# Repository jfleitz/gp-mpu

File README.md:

# GamePlan multi MPU board
This repository contains the KiCad files for designing and creating a GamePlan multi-mpu board for GamePlan pinball machines. The board will work in all upright as well as the cocktail pinball machines.

# Where to Order the board
PCBWay has the latest project files uploaded and verified. The link to order the boards can be found here:
https://www.pcbway.com/project/shareproject/GamePlan_Multi_MPU_Board_601e3e7b.html

# Assembly instructions
Robert Doerr of RobotWorkshop compiled a great assembly guide that can be found [here](docs/GP_Multi_Assembly_V1.3.pdf)

# Status
The board has been tested in several GamePlan machines, both upright and cocktail.

Checkout https://www.epinball.com for the background, current status and additional documentation.

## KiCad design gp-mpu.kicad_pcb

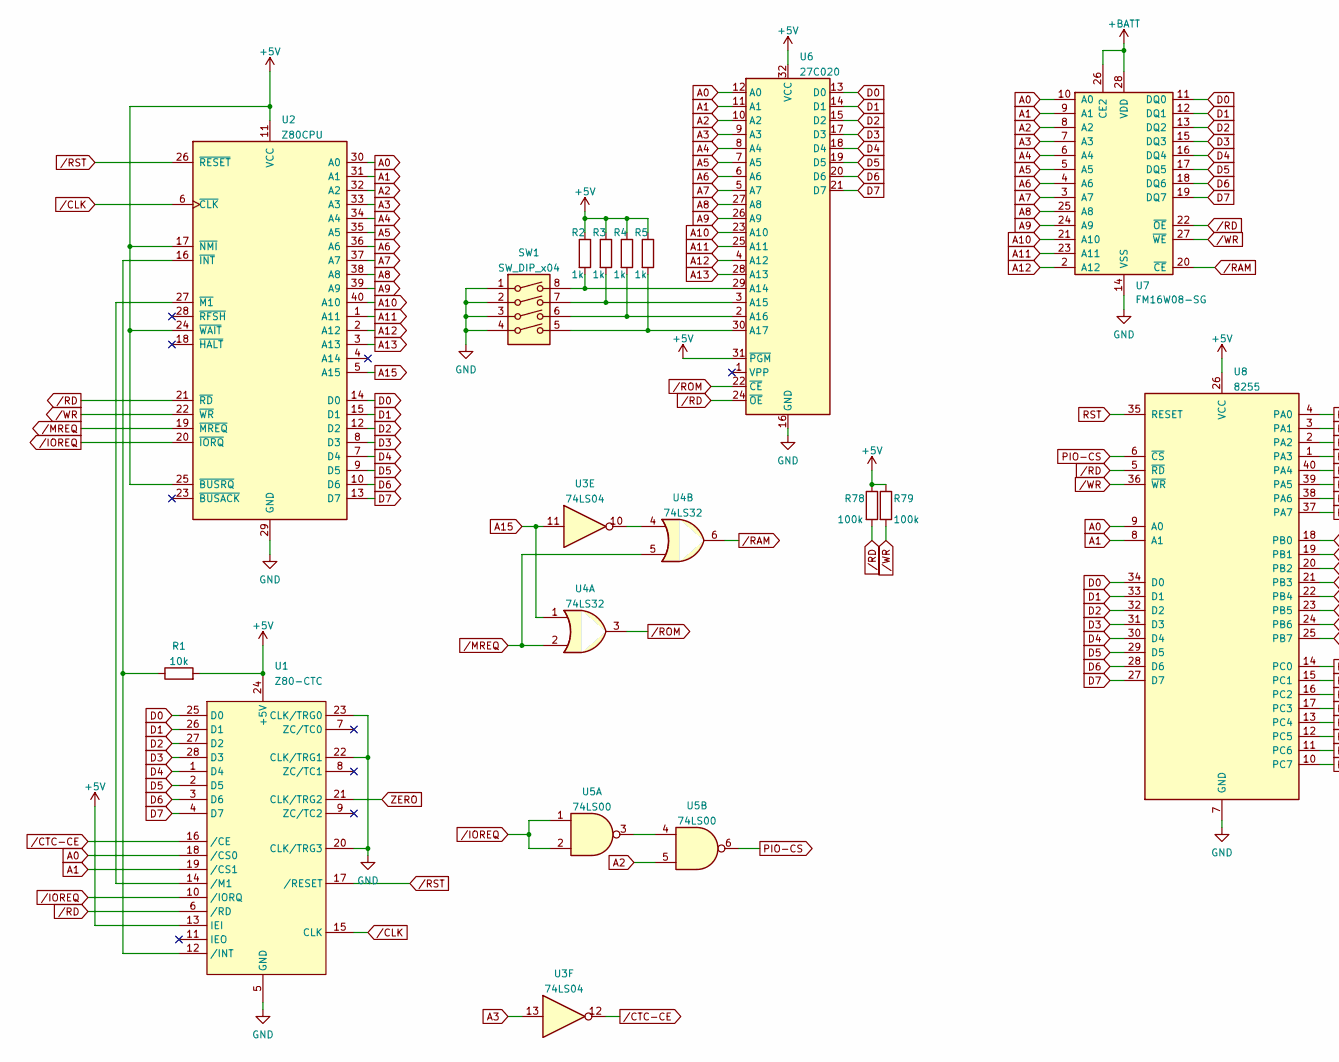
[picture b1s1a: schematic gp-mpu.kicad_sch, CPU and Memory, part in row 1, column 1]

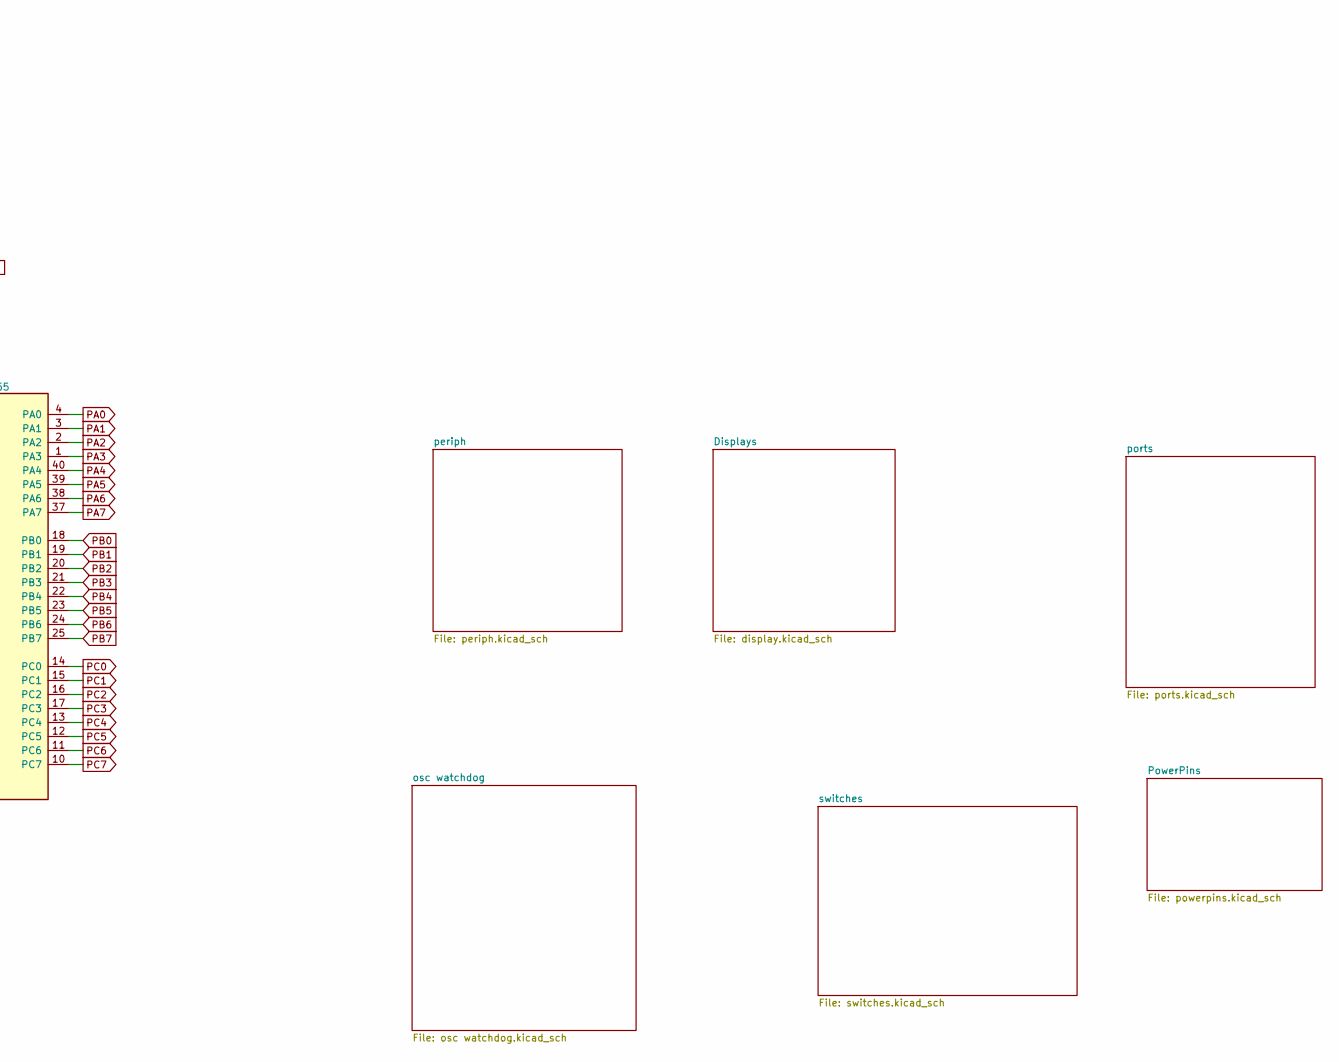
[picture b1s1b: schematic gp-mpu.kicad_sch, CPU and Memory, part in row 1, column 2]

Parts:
R1: 10k; R_Axial_DIN0207_L6.3mm_D2.5mm_P10.16mm_Horizontal
R2, R3, R4, R5: 1k; R_Axial_DIN0207_L6.3mm_D2.5mm_P10.16mm_Horizontal
R78, R79: 100k; R_Axial_DIN0207_L6.3mm_D2.5mm_P10.16mm_Horizontal
SW1: SW_DIP_x04; DIP-8_W7.62mm_LongPads
U1: Z80-CTC; DIP-28_W15.24mm_Socket_LongPads
U2: Z80CPU; DIP-40_W15.24mm_Socket_LongPads
U3: 74LS04; DIP-14_W7.62mm_LongPads
U4: 74LS32; DIP-14_W7.62mm_LongPads
U5: 74LS00; DIP-14_W7.62mm_LongPads
U6: 27C020; DIP-32_W15.24mm_Socket_LongPads
U7: FM16W08-SG; DIP-28_W15.24mm_LongPads
U8: 8255; DIP-40_W15.24mm

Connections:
+5V: R1.2, R2.1, R3.1, R4.1, R5.1, R78.1, R79.1, U1.13 (IEI), U1.24 (+5V), U2.11 (VCC), U2.17 (~NMI), U2.24 (~WAIT), U2.25 (~BUSRQ), U6.31 (~PGM), U6.32 (VCC), U8.26 (VCC); also elsewhere on the board
+BATT: U7.26 (CE2), U7.28 (VDD); also elsewhere on the board
A0: U1.18 (/CS0), U2.30 (A0), U6.12 (A0), U7.10 (A0), U8.9 (A0)
A1: U1.19 (/CS1), U2.31 (A1), U6.11 (A1), U7.9 (A1), U8.8 (A1)
A2: U2.32 (A2), U5.5, U6.10 (A2), U7.8 (A2)
A3: U2.33 (A3), U3.13, U6.9 (A3), U7.7 (A3)
A4: U2.34 (A4), U6.8 (A4), U7.6 (A4)
A5: U2.35 (A5), U6.7 (A5), U7.5 (A5)
A6: U2.36 (A6), U6.6 (A6), U7.4 (A6)
A7: U2.37 (A7), U6.5 (A7), U7.3 (A7)
A8: U2.38 (A8), U6.27 (A8), U7.25 (A8)
A9: U2.39 (A9), U6.26 (A9), U7.24 (A9)
A10: U2.40 (A10), U6.23 (A10), U7.21 (A10)
A11: U2.1 (A11), U6.25 (A11), U7.23 (A11)
A12: U2.2 (A12), U6.4 (A12), U7.2 (A12)
A13: U2.3 (A13), U6.28 (A13)
A15: U2.5 (A15), U3.11, U4.1
D0: U1.25 (D0), U2.14 (D0), U6.13 (D0), U7.11 (DQ0), U8.34 (D0)
D1: U1.26 (D1), U2.15 (D1), U6.14 (D1), U7.12 (DQ1), U8.33 (D1)
D2: U1.27 (D2), U2.12 (D2), U6.15 (D2), U7.13 (DQ2), U8.32 (D2)
D3: U1.28 (D3), U2.8 (D3), U6.17 (D3), U7.15 (DQ3), U8.31 (D3)
D4: U1.1 (D4), U2.7 (D4), U6.18 (D4), U7.16 (DQ4), U8.30 (D4)
D5: U1.2 (D5), U2.9 (D5), U6.19 (D5), U7.17 (DQ5), U8.29 (D5)
D6: U1.3 (D6), U2.10 (D6), U6.20 (D6), U7.18 (DQ6), U8.28 (D6)
D7: U1.4 (D7), U2.13 (D7), U6.21 (D7), U7.19 (DQ7), U8.27 (D7)
GND: SW1.1, SW1.2, SW1.3, SW1.4, U1.5 (GND), U1.20 (CLK/TRG3), U1.22 (CLK/TRG1), U1.23 (CLK/TRG0), U2.29 (GND), U6.16 (GND), U7.14 (VSS), U8.7 (GND); also elsewhere on the board
unnamed: R1.1, U1.12 (/INT), U2.16 (~INT)
unnamed: R2.2, SW1.8, U6.29 (A14)
unnamed: R3.2, SW1.7, U6.3 (A15)
unnamed: R4.2, SW1.6, U6.2 (A16)
unnamed: R5.2, SW1.5, U6.30 (A17)
unnamed: U1.14 (/M1), U2.27 (~M1)
unnamed: U3.10, U4.4
unnamed: U5.3, U5.4
PA0: U8.4 (PA0); also elsewhere on the board
PA1: U8.3 (PA1); also elsewhere on the board
PA2: U8.2 (PA2); also elsewhere on the board
PA3: U8.1 (PA3); also elsewhere on the board
PA4: U8.40 (PA4); also elsewhere on the board
PA5: U8.39 (PA5); also elsewhere on the board
PA6: U8.38 (PA6); also elsewhere on the board
PA7: U8.37 (PA7); also elsewhere on the board
PB0: U8.18 (PB0); also elsewhere on the board
PB1: U8.19 (PB1); also elsewhere on the board
PB2: U8.20 (PB2); also elsewhere on the board
PB3: U8.21 (PB3); also elsewhere on the board
PB4: U8.22 (PB4); also elsewhere on the board
PB5: U8.23 (PB5); also elsewhere on the board
PB6: U8.24 (PB6); also elsewhere on the board
PB7: U8.25 (PB7); also elsewhere on the board
PC0: U8.14 (PC0); also elsewhere on the board
PC1: U8.15 (PC1); also elsewhere on the board
PC2: U8.16 (PC2); also elsewhere on the board
PC3: U8.17 (PC3); also elsewhere on the board
PC4: U8.13 (PC4); also elsewhere on the board
PC5: U8.12 (PC5); also elsewhere on the board
PC6: U8.11 (PC6); also elsewhere on the board
PC7: U8.10 (PC7); also elsewhere on the board
PIO-CS: U5.6, U8.6 (~CS)
RST: U8.35 (RESET); also elsewhere on the board
ZERO: U1.21 (CLK/TRG2); also elsewhere on the board
/CLK: U1.15 (CLK), U2.6 (~CLK); also elsewhere on the board
/CTC-CE: U1.16 (/CE), U3.12
/IOREQ: U1.10 (/IORQ), U2.20 (~IORQ), U5.1, U5.2
/MREQ: U2.19 (~MREQ), U4.2, U4.5
/RAM: U4.6, U7.20 (~CE)
/RD: R78.2, U1.6 (/RD), U2.21 (~RD), U6.24 (~OE), U7.22 (~OE), U8.5 (~RD)
/ROM: U4.3, U6.22 (~CE)
/RST: U1.17 (/RESET), U2.26 (~RESET); also elsewhere on the board
/WR: R79.2, U2.22 (~WR), U7.27 (~WE), U8.36 (~WR)

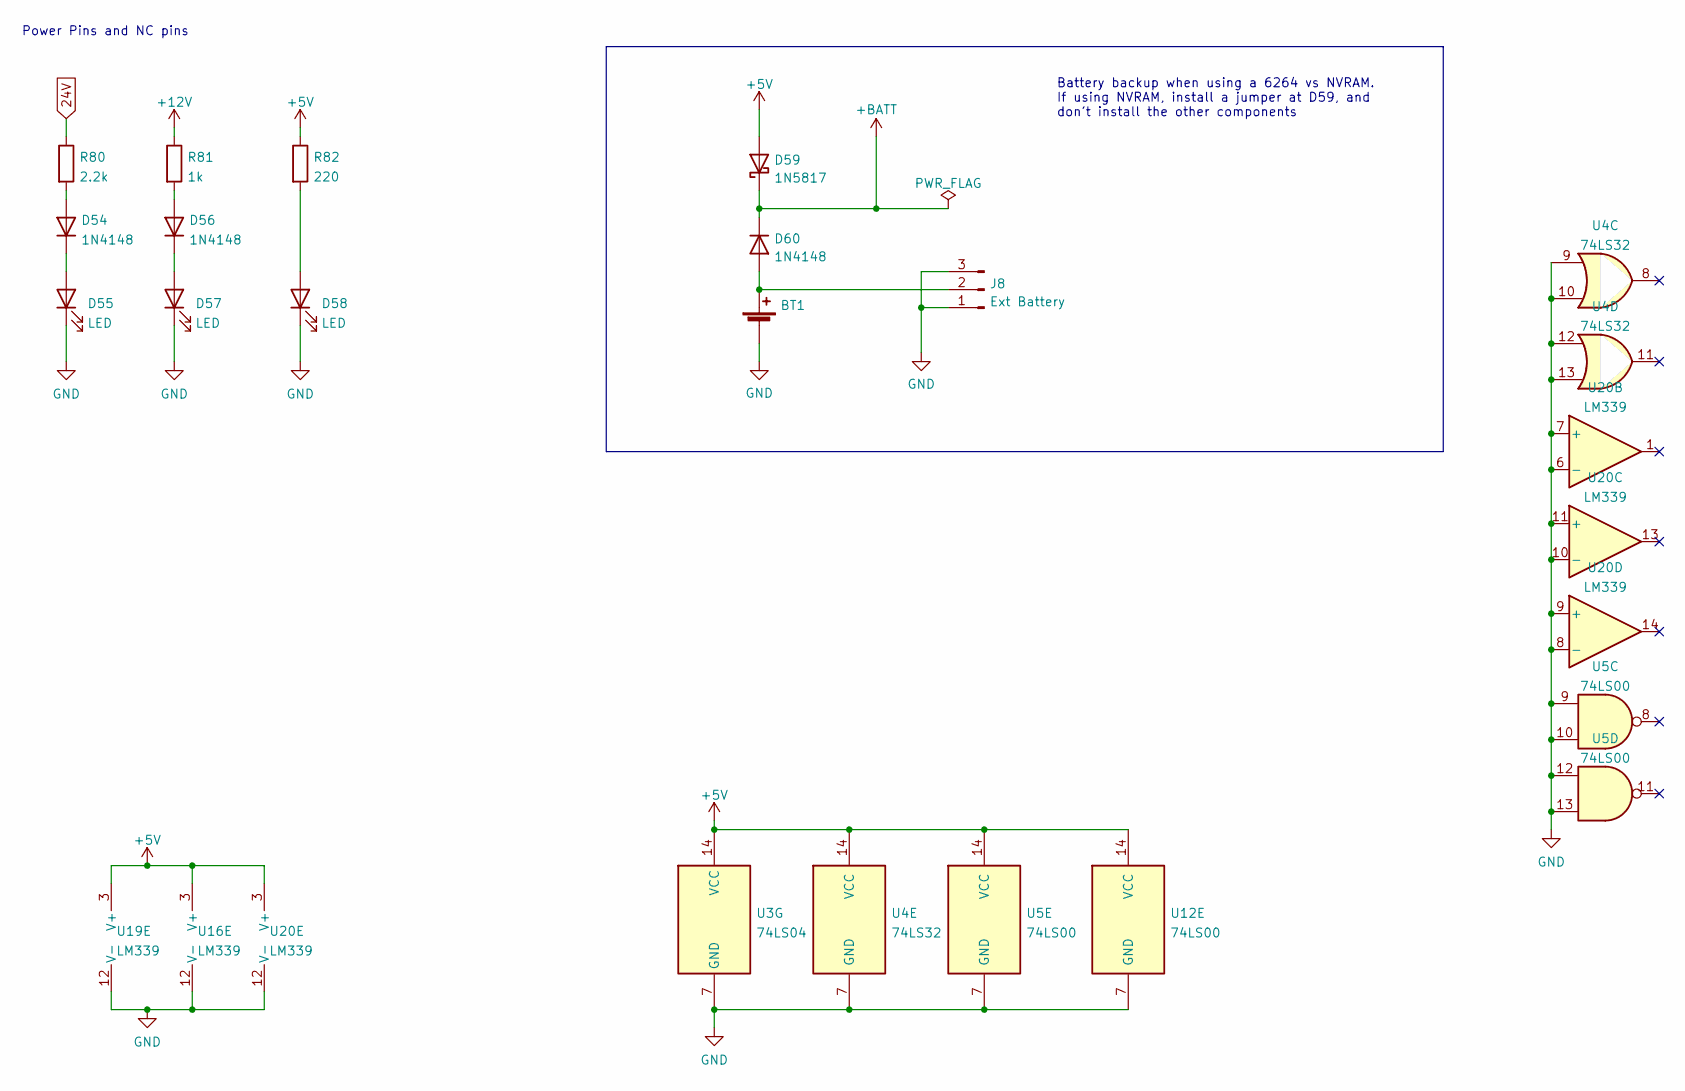
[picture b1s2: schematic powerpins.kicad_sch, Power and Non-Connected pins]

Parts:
BT1: BatteryHolder_ComfortableElectronic_CH273-2450_1x2450
D54, D56, D60: 1N4148; D_DO-35_SOD27_P7.62mm_Horizontal
D55, D57, D58: LED; LED_D3.0mm
D59: 1N5817; D_DO-41_SOD81_P10.16mm_Horizontal
J8: Ext Battery; PinHeader_1x03_P2.54mm_Vertical
R80: 2.2k; R_Axial_DIN0207_L6.3mm_D2.5mm_P10.16mm_Horizontal
R81: 1k; R_Axial_DIN0207_L6.3mm_D2.5mm_P10.16mm_Horizontal
R82: 220; R_Axial_DIN0207_L6.3mm_D2.5mm_P10.16mm_Horizontal
U3: 74LS04; DIP-14_W7.62mm_LongPads
U4: 74LS32; DIP-14_W7.62mm_LongPads
U5, U12: 74LS00; DIP-14_W7.62mm_LongPads
U16, U19, U20: LM339; DIP-14_W7.62mm_LongPads

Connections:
24V: R80.1; also elsewhere on the board
+5V: D59.2 (A), R82.1, U3.14 (VCC), U4.14 (VCC), U5.14 (VCC), U12.14 (VCC), U16.3 (V+), U19.3 (V+), U20.3 (V+); also elsewhere on the board
+12V: R81.1; also elsewhere on the board
+BATT: D59.1 (K), D60.1 (K); also elsewhere on the board
GND: BT1.2 (-), D55.1 (K), D57.1 (K), D58.1 (K), J8.1, J8.3, U3.7 (GND), U4.7 (GND), U4.9, U4.10, U4.12, U4.13, U5.7 (GND), U5.9, U5.10, U5.12, U5.13, U12.7 (GND), U16.12 (V-), U19.12 (V-), U20.6 (-), U20.7 (+), U20.8 (-), U20.9 (+), U20.10 (-), U20.11 (+), U20.12 (V-); also elsewhere on the board
unnamed: BT1.1 (+), D60.2 (A), J8.2
unnamed: D54.1 (K), D55.2 (A)
unnamed: D54.2 (A), R80.2
unnamed: D56.1 (K), D57.2 (A)
unnamed: D56.2 (A), R81.2
unnamed: D58.2 (A), R82.2

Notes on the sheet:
Battery backup when using a 6264 vs NVRAM. If using NVRAM, install a jumper at D59, and don't install the other components
Power Pins and NC pins

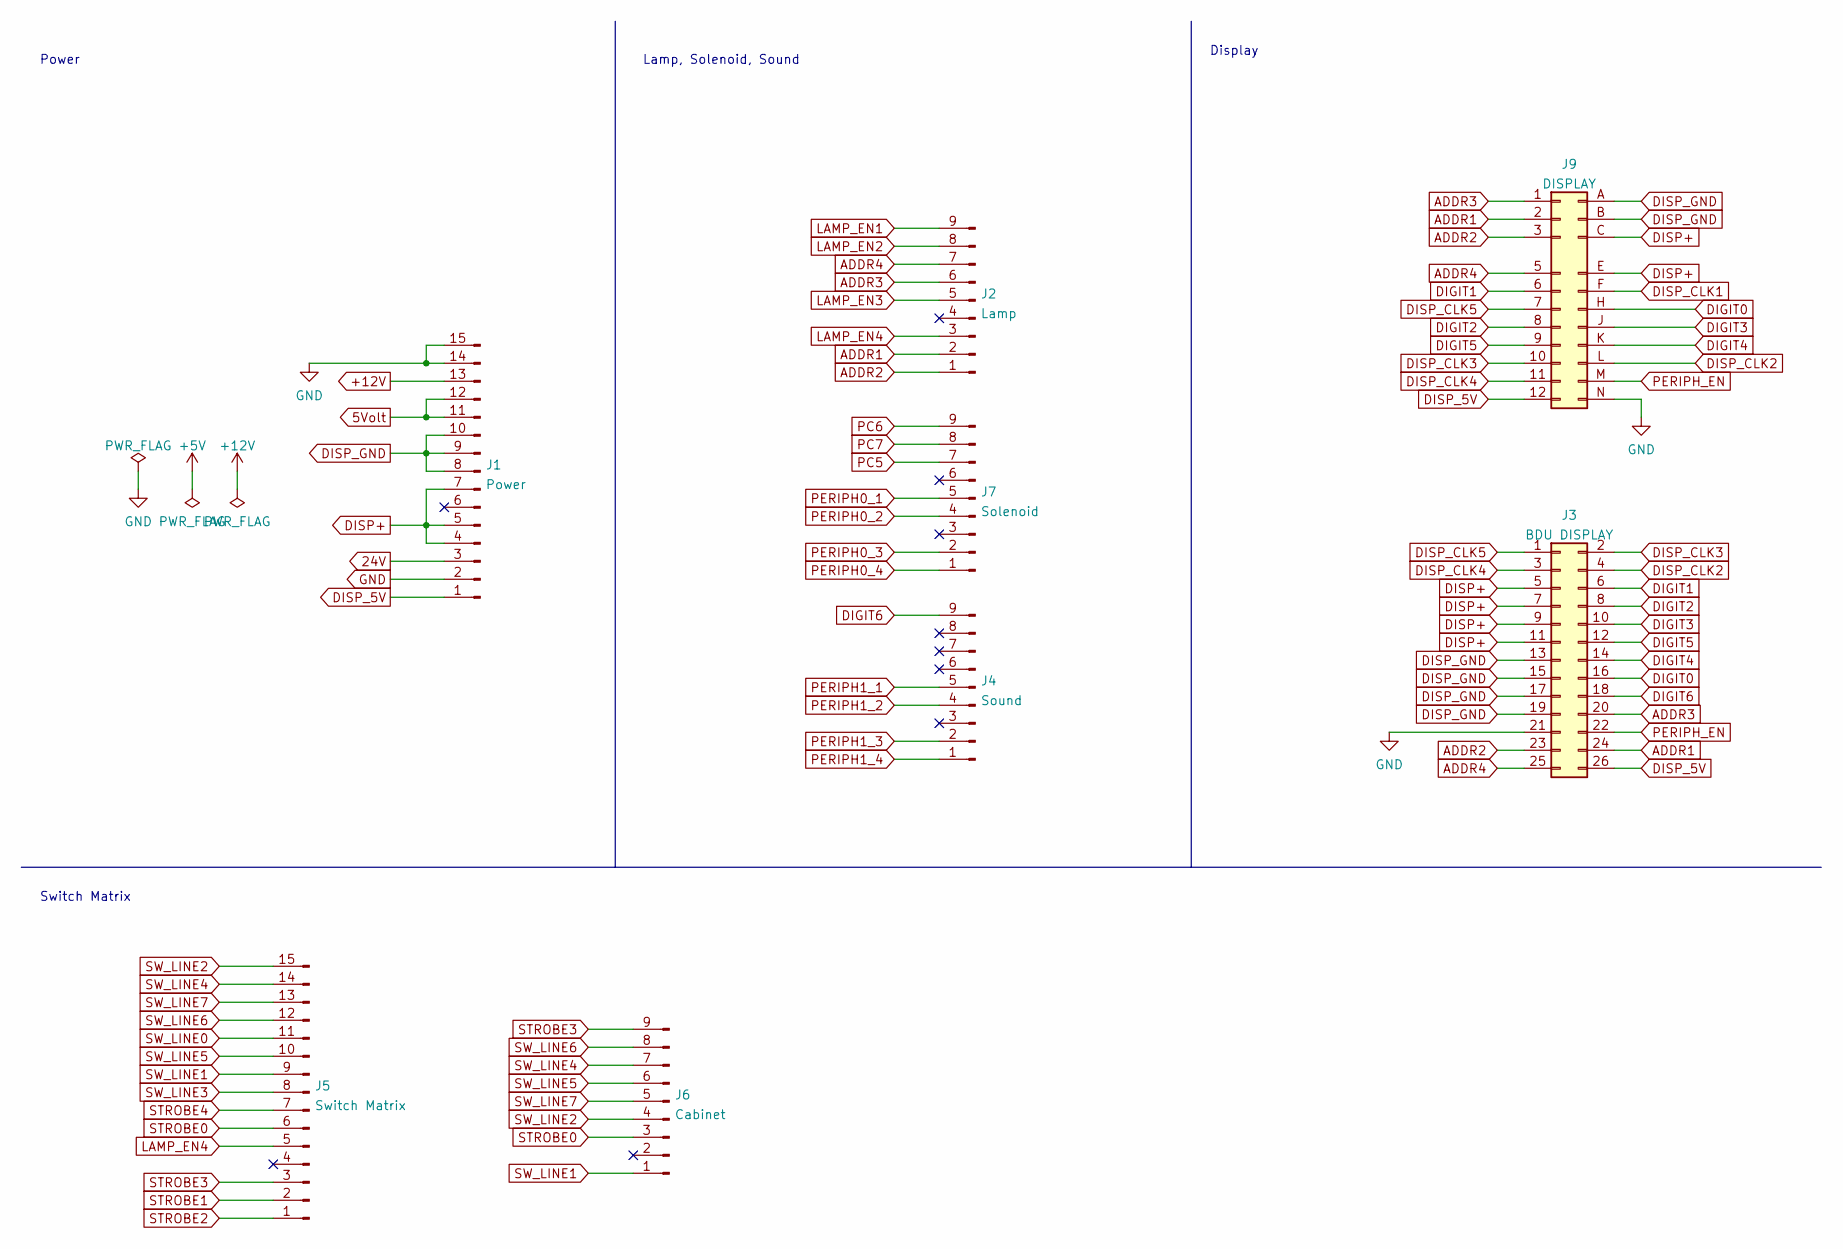
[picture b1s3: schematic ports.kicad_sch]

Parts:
J1: Power; PinHeader_1x15_P2.54mm_Vertical
J2: Lamp; PinHeader_1x09_P2.54mm_Vertical
J3: BDU DISPLAY; display-cocktail
J4: Sound; PinHeader_1x09_P2.54mm_Vertical
J5: Switch Matrix; PinHeader_1x15_P2.54mm_Vertical
J6: Cabinet; PinHeader_1x09_P2.54mm_Vertical
J7: Solenoid; PinHeader_1x09_P2.54mm_Vertical
J9: DISPLAY; display-upright

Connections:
5Volt: J1.11, J1.12; also elsewhere on the board
24V: J1.3; also elsewhere on the board
+12V: J1.13; also elsewhere on the board
ADDR1: J2.2, J3.24, J9.2; also elsewhere on the board
ADDR2: J2.1, J3.23, J9.3; also elsewhere on the board
ADDR3: J2.6, J3.20, J9.1; also elsewhere on the board
ADDR4: J2.7, J3.25, J9.5; also elsewhere on the board
DIGIT0: J3.16, J9.H; also elsewhere on the board
DIGIT1: J3.6, J9.6; also elsewhere on the board
DIGIT2: J3.8, J9.8; also elsewhere on the board
DIGIT3: J3.10, J9.J; also elsewhere on the board
DIGIT4: J3.14, J9.K; also elsewhere on the board
DIGIT5: J3.12, J9.9; also elsewhere on the board
DIGIT6: J3.18, J4.9; also elsewhere on the board
DISP+: J1.4, J1.5, J1.7, J3.5, J3.7, J3.9, J3.11, J9.C, J9.E
DISP_5V: J1.1, J3.26, J9.12
DISP_CLK1: J9.F; also elsewhere on the board
DISP_CLK2: J3.4, J9.L; also elsewhere on the board
DISP_CLK3: J3.2, J9.10; also elsewhere on the board
DISP_CLK4: J3.3, J9.11; also elsewhere on the board
DISP_CLK5: J3.1, J9.7; also elsewhere on the board
DISP_GND: J1.8, J1.9, J1.10, J3.13, J3.15, J3.17, J3.19, J9.A, J9.B
GND: J1.2, J1.14, J1.15, J3.21, J9.N; also elsewhere on the board
LAMP_EN1: J2.9; also elsewhere on the board
LAMP_EN2: J2.8; also elsewhere on the board
LAMP_EN3: J2.5; also elsewhere on the board
LAMP_EN4: J2.3, J5.5; also elsewhere on the board
PC5: J7.7; also elsewhere on the board
PC6: J7.9; also elsewhere on the board
PC7: J7.8; also elsewhere on the board
PERIPH0_1: J7.5; also elsewhere on the board
PERIPH0_2: J7.4; also elsewhere on the board
PERIPH0_3: J7.2; also elsewhere on the board
PERIPH0_4: J7.1; also elsewhere on the board
PERIPH1_1: J4.5; also elsewhere on the board
PERIPH1_2: J4.4; also elsewhere on the board
PERIPH1_3: J4.2; also elsewhere on the board
PERIPH1_4: J4.1; also elsewhere on the board
PERIPH_EN: J3.22, J9.M; also elsewhere on the board
STROBE0: J5.6, J6.3; also elsewhere on the board
STROBE1: J5.2; also elsewhere on the board
STROBE2: J5.1; also elsewhere on the board
STROBE3: J5.3, J6.9; also elsewhere on the board
STROBE4: J5.7; also elsewhere on the board
SW_LINE0: J5.11; also elsewhere on the board
SW_LINE1: J5.9, J6.1; also elsewhere on the board
SW_LINE2: J5.15, J6.4; also elsewhere on the board
SW_LINE3: J5.8; also elsewhere on the board
SW_LINE4: J5.14, J6.7; also elsewhere on the board
SW_LINE5: J5.10, J6.6; also elsewhere on the board
SW_LINE6: J5.12, J6.8; also elsewhere on the board
SW_LINE7: J5.13, J6.5; also elsewhere on the board

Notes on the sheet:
Display
Power
Switch Matrix
Lamp, Solenoid, Sound

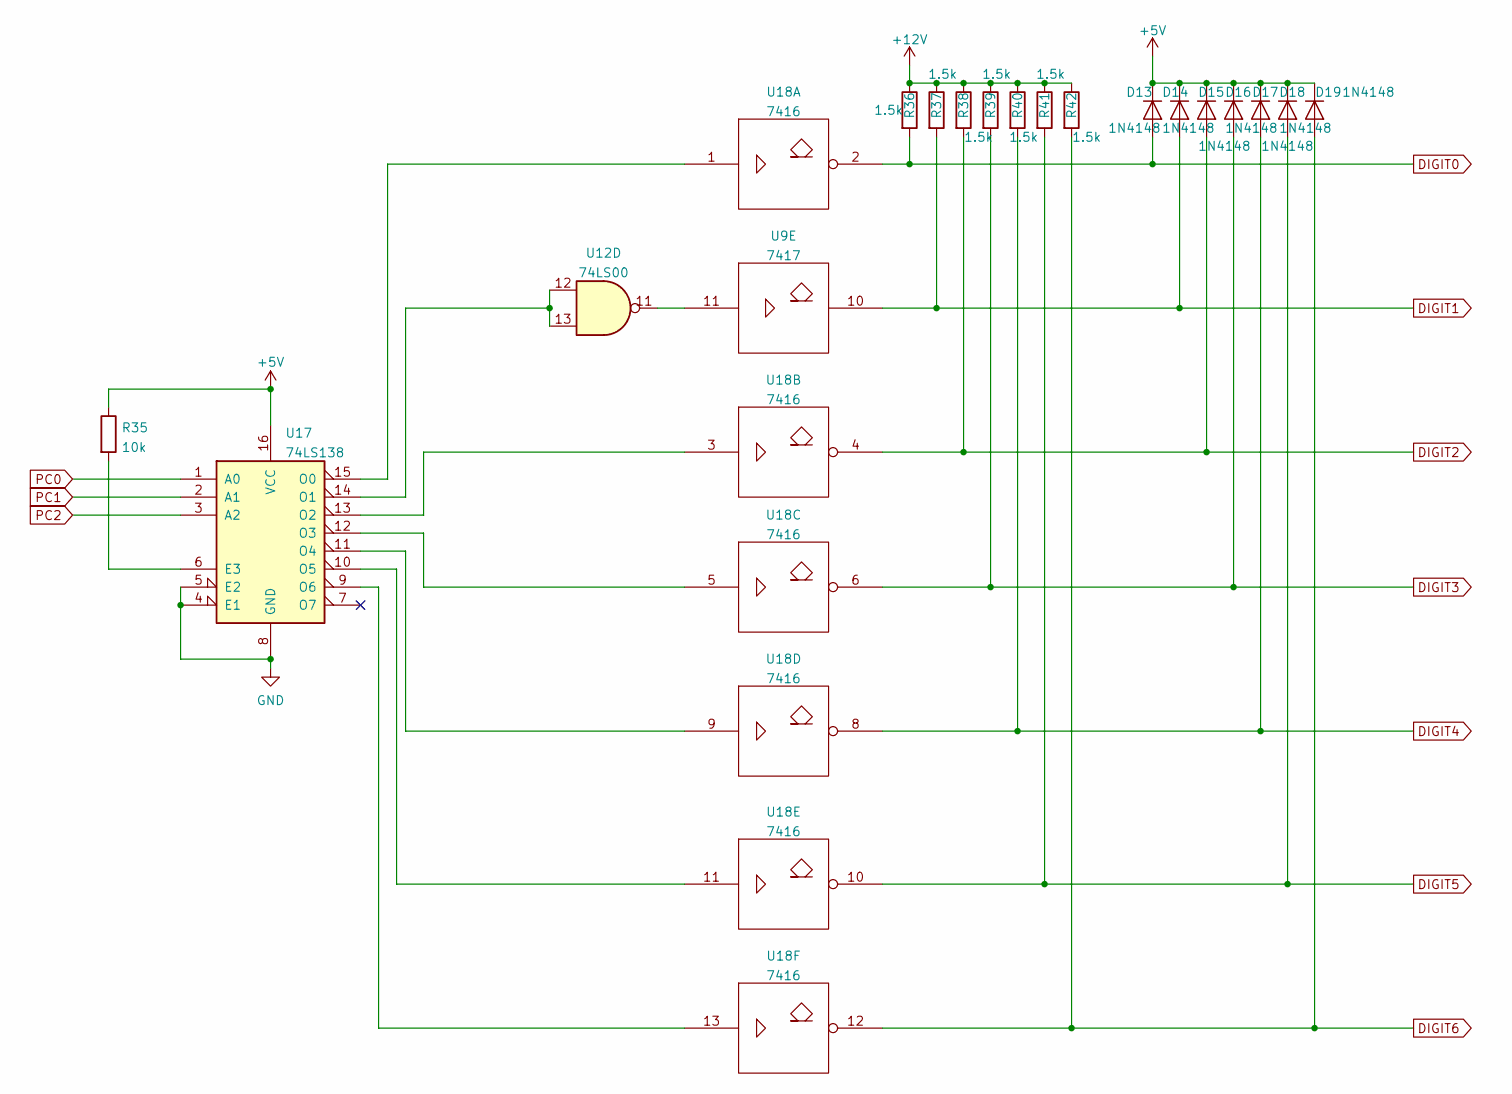
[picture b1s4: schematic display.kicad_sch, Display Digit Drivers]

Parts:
D13, D14, D15, D16, D17, D18, D19: 1N4148; D_DO-35_SOD27_P7.62mm_Horizontal
R35: 10k; R_Axial_DIN0207_L6.3mm_D2.5mm_P10.16mm_Horizontal
R36, R37, R38, R39, R40, R41, R42: 1.5k; R_Axial_DIN0207_L6.3mm_D2.5mm_P10.16mm_Horizontal
U9: 7417; DIP-14_W7.62mm_LongPads
U12: 74LS00; DIP-14_W7.62mm_LongPads
U17: 74LS138; DIP-16_W7.62mm_LongPads
U18: 7416; DIP-14_W7.62mm_LongPads

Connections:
+5V: D13.1 (K), D14.1 (K), D15.1 (K), D16.1 (K), D17.1 (K), D18.1 (K), D19.1 (K), R35.1, U9.14 (Vcc), U17.16 (VCC), U18.14 (Vcc); also elsewhere on the board
+12V: R36.1, R37.1, R38.1, R39.1, R40.1, R41.1, R42.1; also elsewhere on the board
DIGIT0: D13.2 (A), R36.2, U18.2; also elsewhere on the board
DIGIT1: D14.2 (A), R37.2, U9.10; also elsewhere on the board
DIGIT2: D15.2 (A), R38.2, U18.4; also elsewhere on the board
DIGIT3: D16.2 (A), R39.2, U18.6; also elsewhere on the board
DIGIT4: D17.2 (A), R40.2, U18.8; also elsewhere on the board
DIGIT5: D18.2 (A), R41.2, U18.10; also elsewhere on the board
DIGIT6: D19.2 (A), R42.2, U18.12; also elsewhere on the board
GND: U9.7 (Gnd), U17.4 (E1), U17.5 (E2), U17.8 (GND), U18.7 (Gnd); also elsewhere on the board
unnamed: R35.2, U17.6 (E3)
unnamed: U9.11, U12.11
unnamed: U12.12, U12.13, U17.14 (O1)
unnamed: U17.9 (O6), U18.13
unnamed: U17.10 (O5), U18.11
unnamed: U17.11 (O4), U18.9
unnamed: U17.12 (O3), U18.5
unnamed: U17.13 (O2), U18.3
unnamed: U17.15 (O0), U18.1
PC0: U17.1 (A0); also elsewhere on the board
PC1: U17.2 (A1); also elsewhere on the board
PC2: U17.3 (A2); also elsewhere on the board

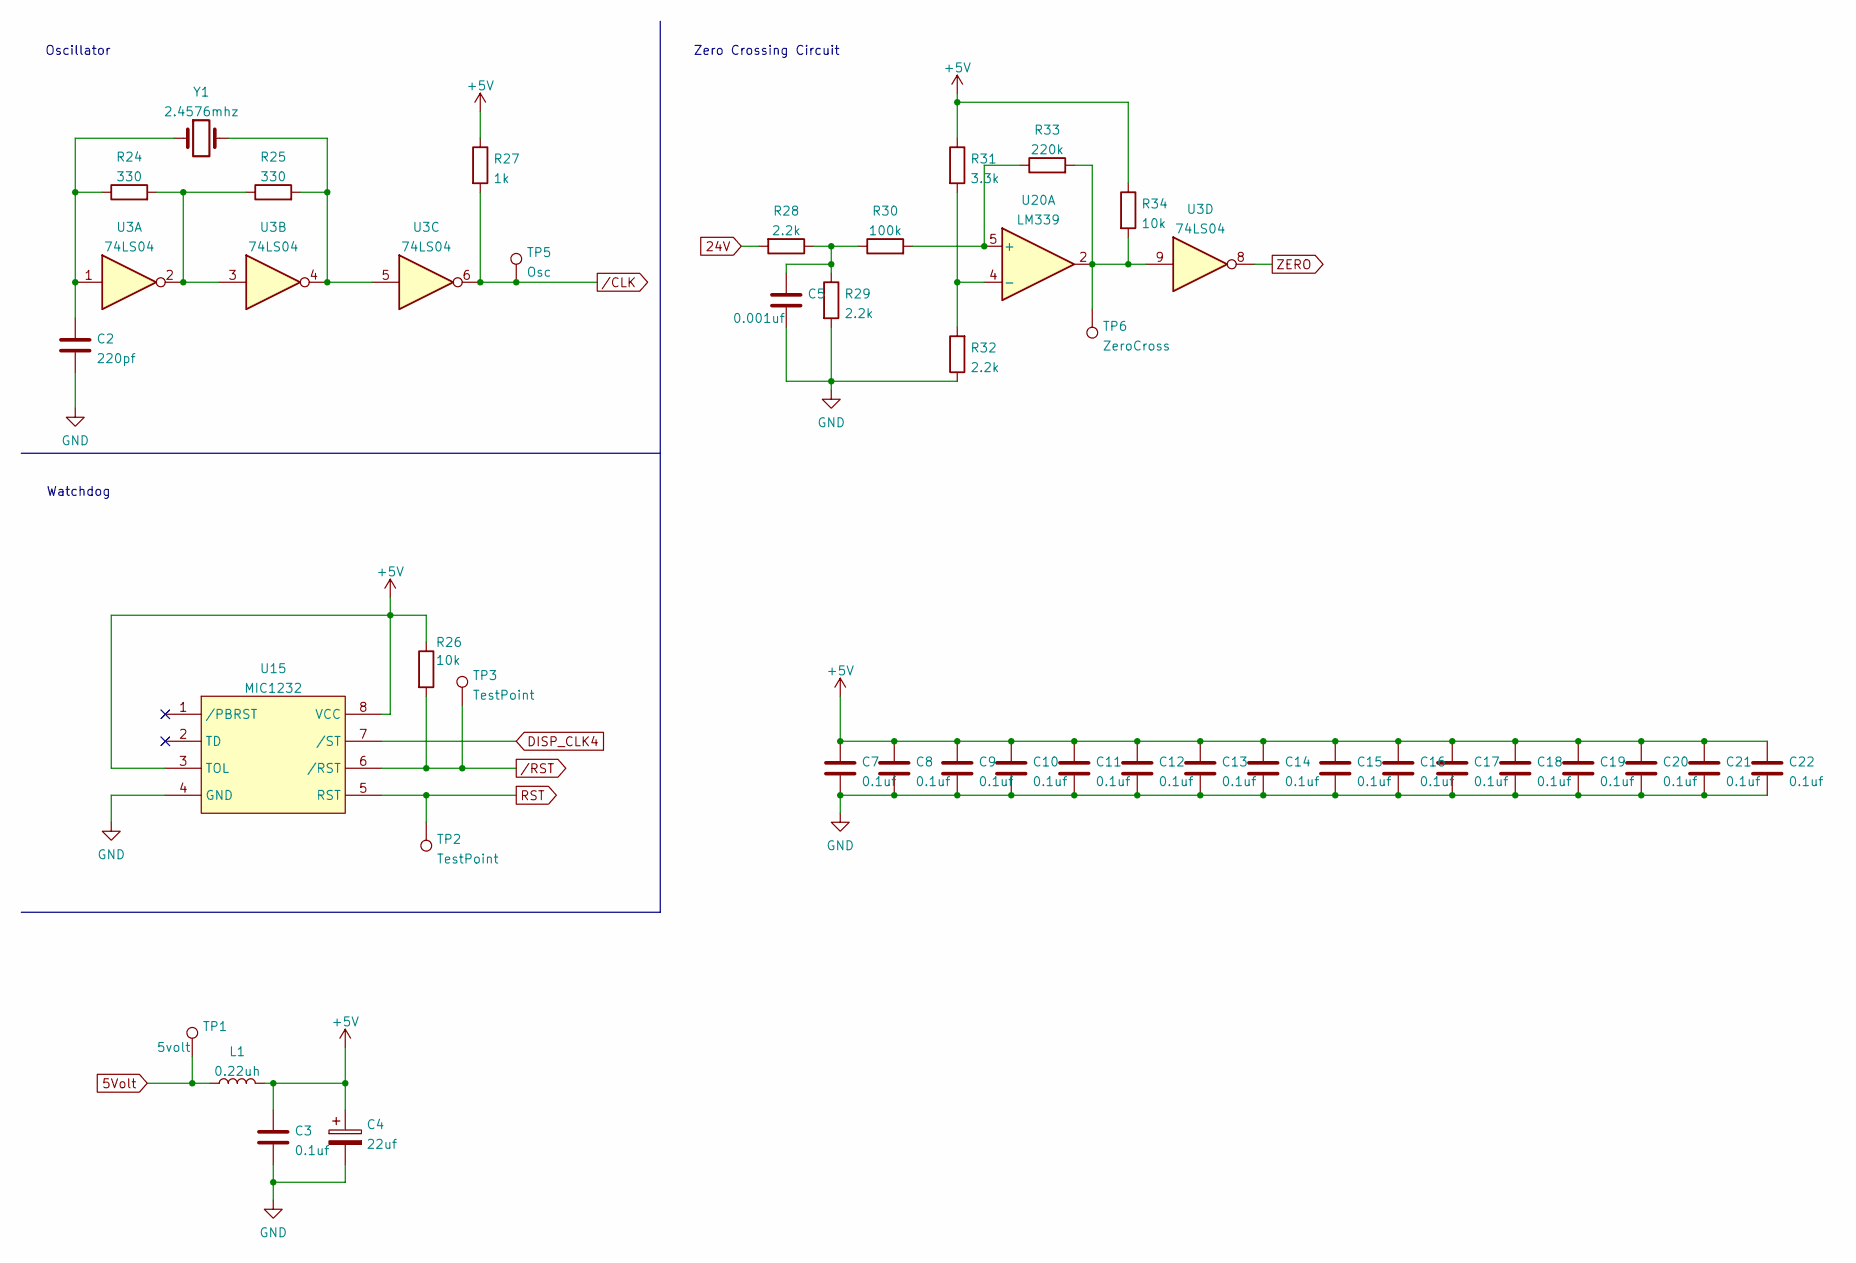
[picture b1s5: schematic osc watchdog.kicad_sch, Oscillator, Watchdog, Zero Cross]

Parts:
C2: 220pf; C_Disc_D5.0mm_W2.5mm_P2.50mm
C3, C7, C8, C9, C10, C11, C12, C13, C14, C15, C16, C17, C18, C19, C20, C21, C22: 0.1uf; C_Disc_D5.0mm_W2.5mm_P5.00mm
C4: 22uf; CP_Radial_D5.0mm_P2.50mm
C5: 0.001uf; C_Disc_D5.0mm_W2.5mm_P5.00mm
L1: 0.22uh; L_Axial_L5.3mm_D2.2mm_P10.16mm_Horizontal_Vishay_IM-1
R24, R25: 330; R_Axial_DIN0207_L6.3mm_D2.5mm_P10.16mm_Horizontal
R26, R34: 10k; R_Axial_DIN0207_L6.3mm_D2.5mm_P10.16mm_Horizontal
R27: 1k; R_Axial_DIN0207_L6.3mm_D2.5mm_P10.16mm_Horizontal
R28, R29, R32: 2.2k; R_Axial_DIN0207_L6.3mm_D2.5mm_P10.16mm_Horizontal
R30: 100k; R_Axial_DIN0207_L6.3mm_D2.5mm_P10.16mm_Horizontal
R31: 3.3k; R_Axial_DIN0207_L6.3mm_D2.5mm_P10.16mm_Horizontal
R33: 220k; R_Axial_DIN0207_L6.3mm_D2.5mm_P10.16mm_Horizontal
TP1: 5volt; TestPoint_Pad_D3.0mm
TP2, TP3: TestPoint; TestPoint_Pad_D3.0mm
TP5: Osc; TestPoint_Pad_D3.0mm
TP6: ZeroCross; TestPoint_Pad_D3.0mm
U3: 74LS04; DIP-14_W7.62mm_LongPads
U15: MIC1232; DIP-8_W7.62mm_LongPads
U20: LM339; DIP-14_W7.62mm_LongPads
Y1: 2.4576mhz; Crystal_HC18-U_Horizontal

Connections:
5Volt: L1.1, TP1.1; also elsewhere on the board
24V: R28.2; also elsewhere on the board
+5V: C3.1, C4.1, C7.1, C8.1, C9.1, C10.1, C11.1, C12.1, C13.1, C14.1, C15.1, C16.1, C17.1, C18.1, C19.1, C20.1, C21.1, C22.1, L1.2, R26.1, R27.1, R31.1, R34.1, U15.3 (TOL), U15.8 (VCC); also elsewhere on the board
DISP_CLK4: U15.7 (/ST); also elsewhere on the board
GND: C2.2, C3.2, C4.2, C5.2, C7.2, C8.2, C9.2, C10.2, C11.2, C12.2, C13.2, C14.2, C15.2, C16.2, C17.2, C18.2, C19.2, C20.2, C21.2, C22.2, R29.2, R32.1, U15.4 (GND); also elsewhere on the board
unnamed: C2.1, R24.1, U3.1, Y1.1
unnamed: C5.1, R28.1, R29.1, R30.1
unnamed: R24.2, R25.1, U3.2, U3.3
unnamed: R25.2, U3.4, U3.5, Y1.2
unnamed: R30.2, R33.1, U20.5 (+)
unnamed: R31.2, R32.2, U20.4 (-)
unnamed: R33.2, R34.2, TP6.1, U3.9, U20.2
RST: TP2.1, U15.5 (RST); also elsewhere on the board
ZERO: U3.8; also elsewhere on the board
/CLK: R27.2, TP5.1, U3.6; also elsewhere on the board
/RST: R26.2, TP3.1, U15.6 (/RST); also elsewhere on the board

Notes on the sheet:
Oscillator
Watchdog
Zero Crossing Circuit
